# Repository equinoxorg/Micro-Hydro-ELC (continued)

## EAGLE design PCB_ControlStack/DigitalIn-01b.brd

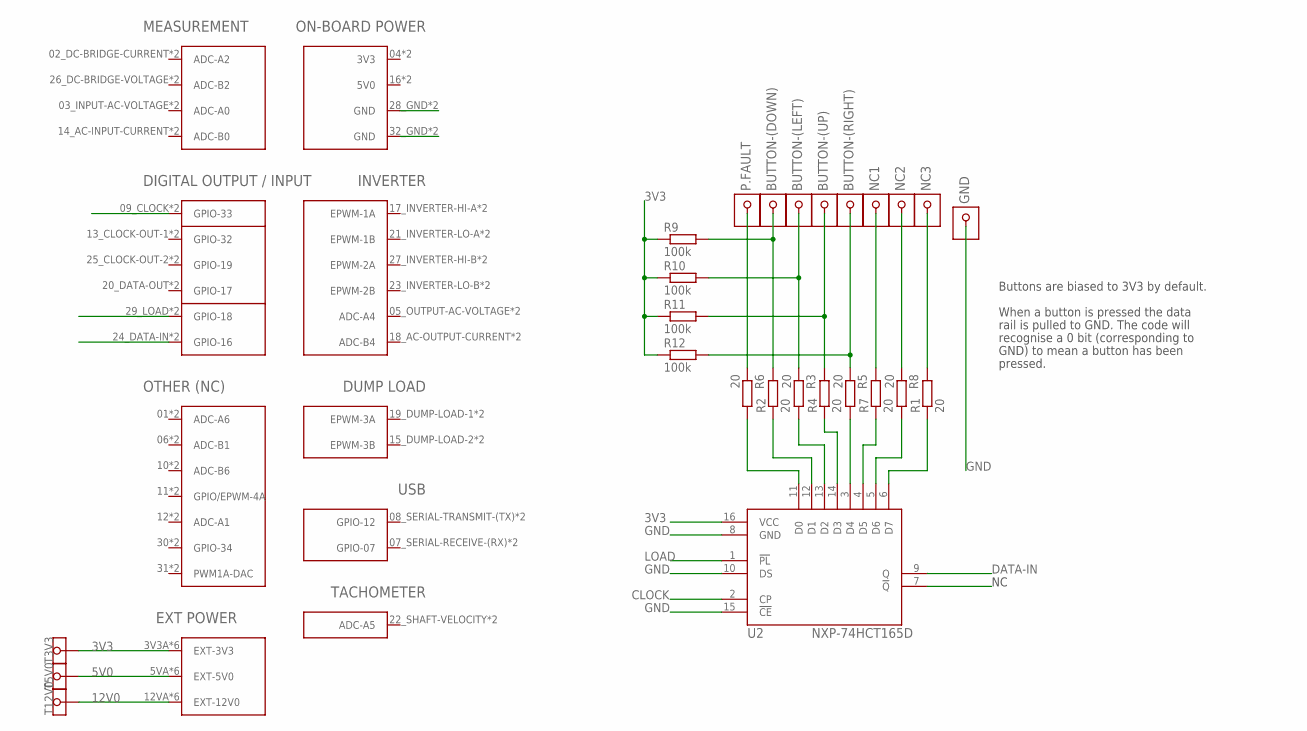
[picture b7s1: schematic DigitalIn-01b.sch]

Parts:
BUTTON-(DOWN): 1X1HEADER(W/VIA)
BUTTON-(LEFT): 1X1HEADER(W/VIA)
BUTTON-(RIGHT): 1X1HEADER(W/VIA)
BUTTON-(UP): 1X1HEADER(W/VIA)
GND: 1X1HEADER(W/VIA)
NC1, NC2, NC3: 1X1HEADER(W/VIA)
P.FAULT: 1X1HEADER(W/VIA)
R1, R2, R3, R4, R5, R6, R7, R8: 20; R0805
R9, R10, R11, R12: 100k; R0805
T3V3, T5V0, T12V0: TESTPAD
U1: CONTROLLER_STACK
U2: NXP-74HCT165D; SOIC-16D

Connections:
3V3: R9.1, R10.1, R11.1, R12.1, T3V3.TP, U1.3V3A (EXT-3V3), U1.3V3B (EXT-3V3), U1.3V3C (EXT-3V3), U1.3V3D (EXT-3V3), U1.3V3E (EXT-3V3), U1.3V3F (EXT-3V3), U2.16 (VCC)
5V0: T5V0.TP, U1.5VA (EXT-5V0), U1.5VB (EXT-5V0), U1.5VC (EXT-5V0), U1.5VD (EXT-5V0), U1.5VE (EXT-5V0), U1.5VF (EXT-5V0)
12V0: T12V0.TP, U1.12VA (EXT-12V0), U1.12VB (EXT-12V0), U1.12VC (EXT-12V0), U1.12VD (EXT-12V0), U1.12VE (EXT-12V0), U1.12VF (EXT-12V0)
CLOCK: U1.09_CLOCK (GPIO-33), U1.C9 (GPIO-33), U2.2 (CP)
DATA-IN: U1.24_DATA-IN (GPIO-16), U1.C24 (GPIO-16), U2.9 (Q)
GND: GND.P$2, GND.P$3, GND.P$4, GND.PAD, U1.28_GND (GND), U1.32_GND (GND), U1.C28 (GND), U1.C32 (GND), U2.8 (GND), U2.10 (DS), U2.15 (!CE)
LOAD: U1.29_LOAD (GPIO-18), U1.C29 (GPIO-18), U2.1 (!PL)
unnamed: R6.2, U2.11 (D0)
unnamed: R2.1, U2.12 (D1)
unnamed: R3.2, U2.13 (D2)
unnamed: R4.1, U2.14 (D3)
unnamed: P.FAULT.P$2, P.FAULT.P$3, P.FAULT.P$4, P.FAULT.PAD, R6.1
unnamed: R7.1, U2.4 (D5)
unnamed: R8.2, U2.5 (D6)
unnamed: R1.1, U2.6 (D7)
unnamed: R5.2, U2.3 (D4)
unnamed: BUTTON-(DOWN).P$2, BUTTON-(DOWN).P$3, BUTTON-(DOWN).P$4, BUTTON-(DOWN).PAD, R2.2, R9.2
unnamed: BUTTON-(LEFT).P$2, BUTTON-(LEFT).P$3, BUTTON-(LEFT).P$4, BUTTON-(LEFT).PAD, R3.1, R10.2
unnamed: BUTTON-(UP).P$2, BUTTON-(UP).P$3, BUTTON-(UP).P$4, BUTTON-(UP).PAD, R4.2, R11.2
unnamed: BUTTON-(RIGHT).P$2, BUTTON-(RIGHT).P$3, BUTTON-(RIGHT).P$4, BUTTON-(RIGHT).PAD, R5.1, R12.2
unnamed: NC1.P$2, NC1.P$3, NC1.P$4, NC1.PAD, R7.2
unnamed: NC2.P$2, NC2.P$3, NC2.P$4, NC2.PAD, R8.1
unnamed: NC3.P$2, NC3.P$3, NC3.P$4, NC3.PAD, R1.2

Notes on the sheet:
Buttons are biased to 3V3 by default.
When a button is pressed the data
rail is pulled to GND. The code will
recognise a 0 bit (corresponding to
GND) to mean a button has been
pressed.

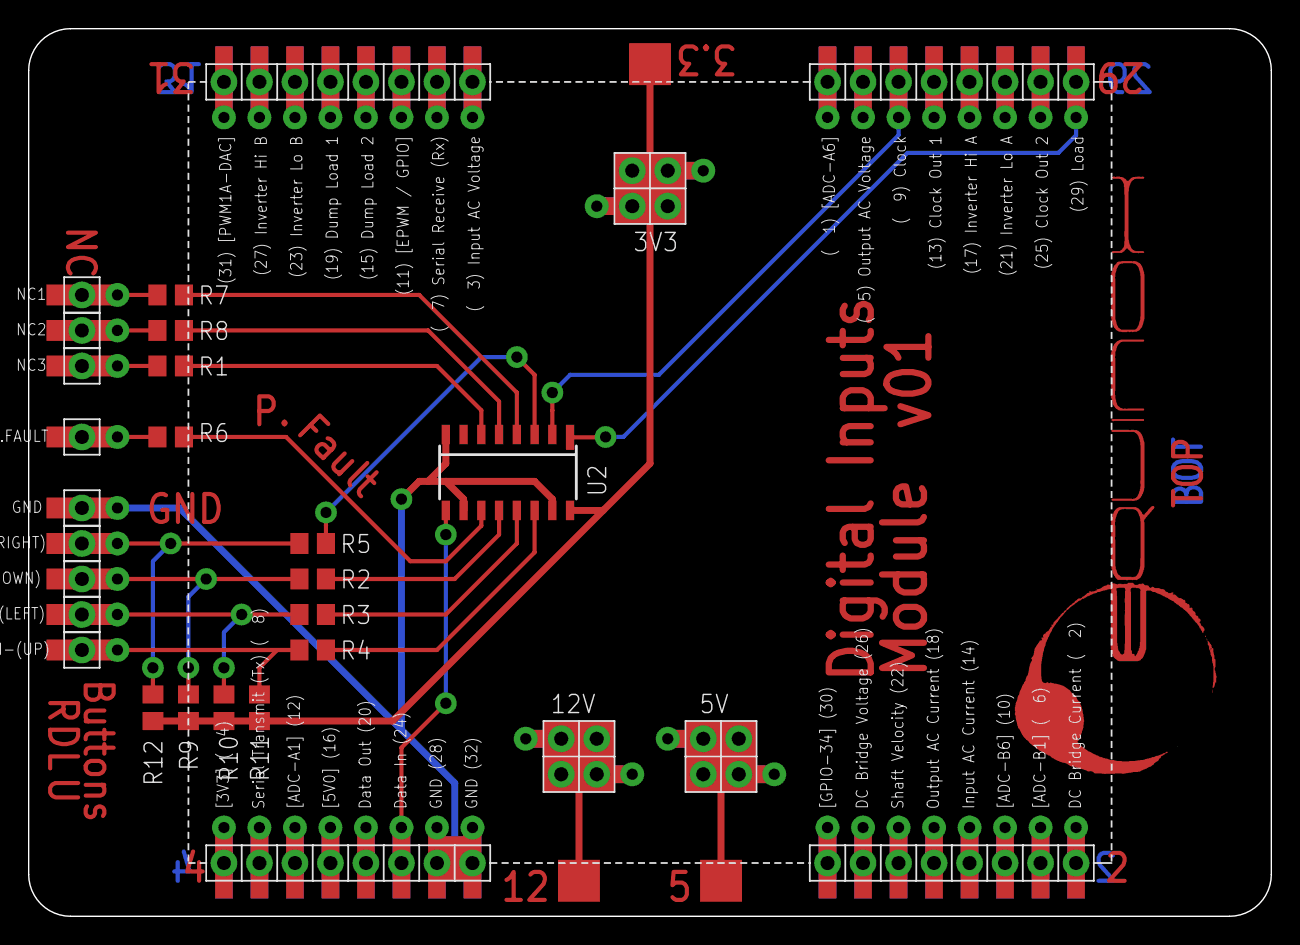
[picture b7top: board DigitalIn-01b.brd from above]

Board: 2 copper layers, 88.9 x 63.5 mm, 26 parts (0 on the bottom side), 23 nets.

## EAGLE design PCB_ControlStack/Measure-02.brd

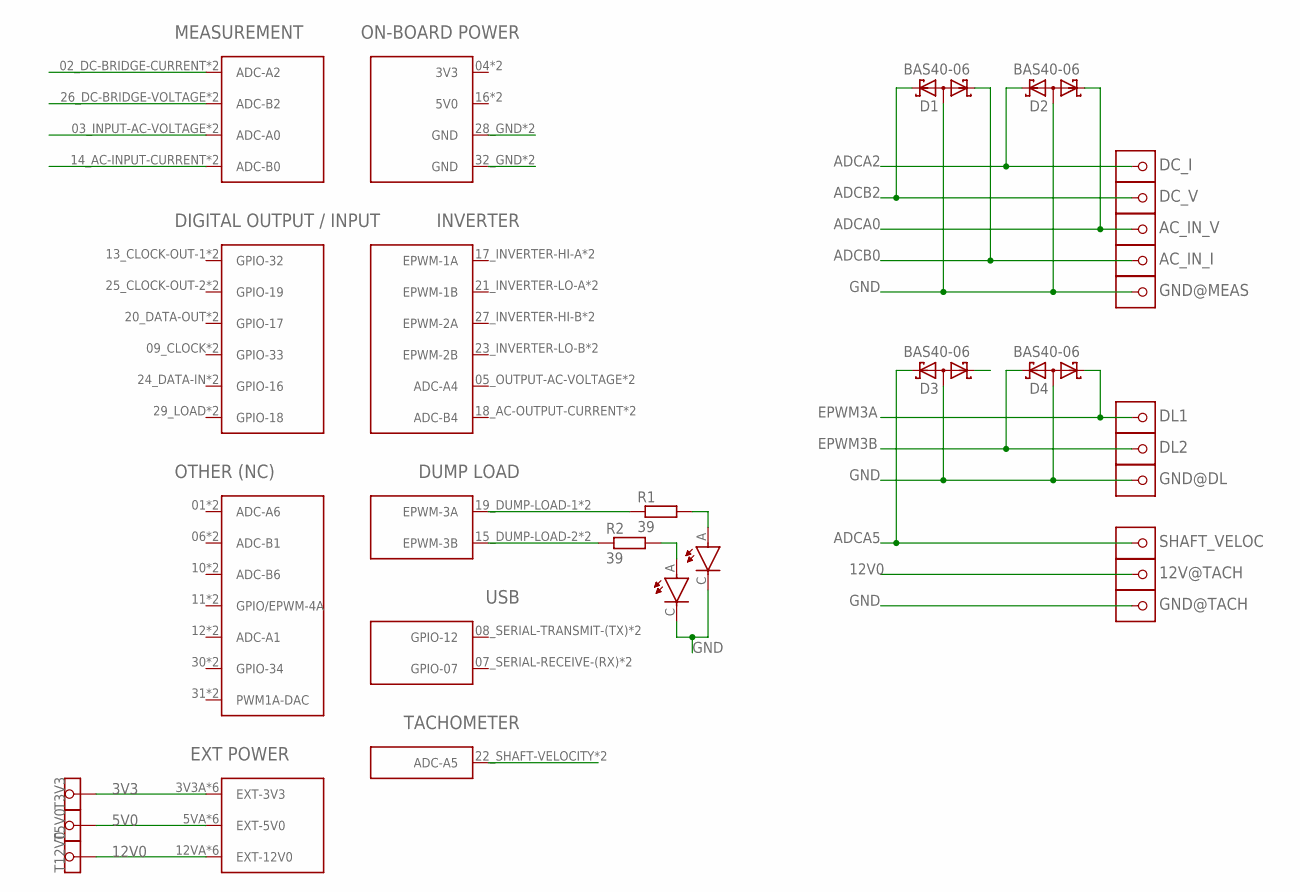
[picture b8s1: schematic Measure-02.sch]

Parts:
12V@TACH: 1X1HEADER(W/VIA)
AC_IN_I: 1X1HEADER(W/VIA)
AC_IN_V: 1X1HEADER(W/VIA)
D1, D2, D3, D4: BAS40-06; SOT23
DC_I: 1X1HEADER(W/VIA)
DC_V: 1X1HEADER(W/VIA)
DL1, DL2: 1X1HEADER(W/VIA)
DL.1, DL.2: PLCC2
GND@DL: 1X1HEADER(W/VIA)
GND@MEAS: 1X1HEADER(W/VIA)
GND@TACH: 1X1HEADER(W/VIA)
R1, R2: 39; R0805
SHAFT_VELOC: 1X1HEADER(W/VIA)
T3V3, T5V0, T12V0: TESTPAD
U$1: CONTROLLER_STACK

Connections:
3V3: T3V3.TP, U$1.3V3A (EXT-3V3), U$1.3V3B (EXT-3V3), U$1.3V3C (EXT-3V3), U$1.3V3D (EXT-3V3), U$1.3V3E (EXT-3V3), U$1.3V3F (EXT-3V3)
5V0: T5V0.TP, U$1.5VA (EXT-5V0), U$1.5VB (EXT-5V0), U$1.5VC (EXT-5V0), U$1.5VD (EXT-5V0), U$1.5VE (EXT-5V0), U$1.5VF (EXT-5V0)
12V0: 12V@TACH.P$2, 12V@TACH.P$3, 12V@TACH.P$4, 12V@TACH.PAD, T12V0.TP, U$1.12VA (EXT-12V0), U$1.12VB (EXT-12V0), U$1.12VC (EXT-12V0), U$1.12VD (EXT-12V0), U$1.12VE (EXT-12V0), U$1.12VF (EXT-12V0)
ADCA0: AC_IN_V.P$2, AC_IN_V.P$3, AC_IN_V.P$4, AC_IN_V.PAD, D2.1 (K1), U$1.03_INPUT-AC-VOLTAGE (ADC-A0), U$1.C3 (ADC-A0)
ADCA2: D2.2 (K2), DC_I.P$2, DC_I.P$3, DC_I.P$4, DC_I.PAD, U$1.02_DC-BRIDGE-CURRENT (ADC-A2), U$1.C2 (ADC-A2)
ADCA5: D3.2 (K2), SHAFT_VELOC.P$2, SHAFT_VELOC.P$3, SHAFT_VELOC.P$4, SHAFT_VELOC.PAD, U$1.22_SHAFT-VELOCITY (ADC-A5), U$1.C22 (ADC-A5)
ADCB0: AC_IN_I.P$2, AC_IN_I.P$3, AC_IN_I.P$4, AC_IN_I.PAD, D1.1 (K1), U$1.14_AC-INPUT-CURRENT (ADC-B0), U$1.C14 (ADC-B0)
ADCB2: D1.2 (K2), DC_V.P$2, DC_V.P$3, DC_V.P$4, DC_V.PAD, U$1.26_DC-BRIDGE-VOLTAGE (ADC-B2), U$1.C26 (ADC-B2)
EPWM3A: D4.1 (K1), DL1.P$2, DL1.P$3, DL1.P$4, DL1.PAD, R1.1, U$1.19_DUMP-LOAD-1 (EPWM-3A), U$1.C19 (EPWM-3A)
EPWM3B: D4.2 (K2), DL2.P$2, DL2.P$3, DL2.P$4, DL2.PAD, R2.1, U$1.15_DUMP-LOAD-2 (EPWM-3B), U$1.C15 (EPWM-3B)
GND: D1.3 (AA), D2.3 (AA), D3.3 (AA), D4.3 (AA), DL.1.C, DL.2.C, GND@DL.P$2, GND@DL.P$3, GND@DL.P$4, GND@DL.PAD, GND@MEAS.P$2, GND@MEAS.P$3, GND@MEAS.P$4, GND@MEAS.PAD, GND@TACH.P$2, GND@TACH.P$3, GND@TACH.P$4, GND@TACH.PAD, U$1.28_GND (GND), U$1.32_GND (GND), U$1.C28 (GND), U$1.C32 (GND)
unnamed: DL.2.A, R2.2
unnamed: DL.1.A, R1.2
STARTUP: D3.1 (K1)

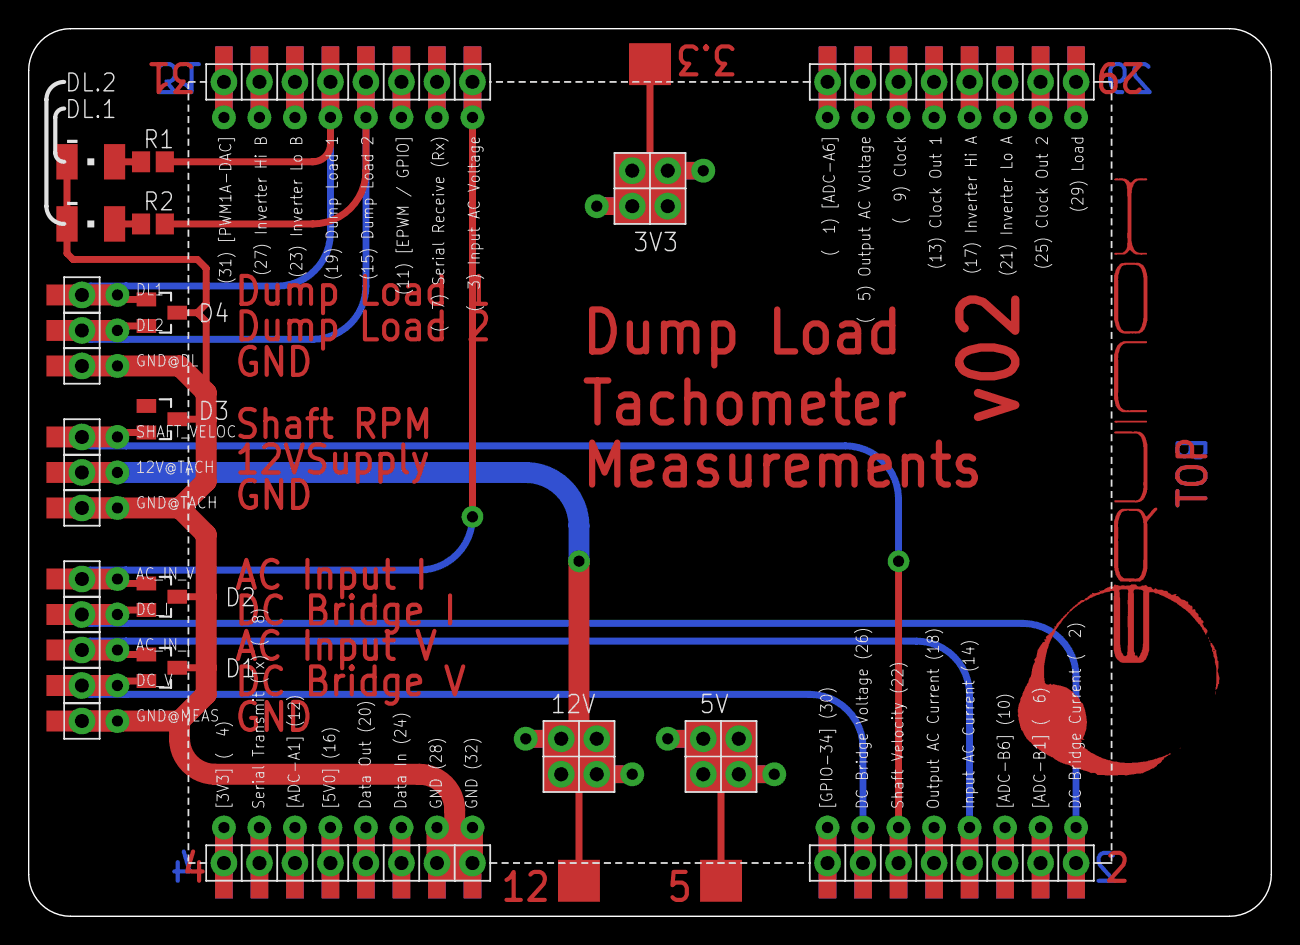
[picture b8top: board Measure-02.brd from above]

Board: 2 copper layers, 88.9 x 63.5 mm, 23 parts (0 on the bottom side), 13 nets.

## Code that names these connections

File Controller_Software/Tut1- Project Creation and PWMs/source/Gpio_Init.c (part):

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	GpioCtrlRegs.GPADIR.all   = 0x00000000;		// All group A GPIO are inputs
	GpioCtrlRegs.GPAPUD.all   = 0x00000FFF;		// Pull-ups enabled GPIO31-12, disabled GPIO11-0

	GpioCtrlRegs.GPAMUX1.bit.GPIO0  = 0;		// 0=GPIO               1=EPWM1A     2=rsvd       3=rsvd
	GpioCtrlRegs.GPAMUX1.bit.GPIO1  = 0;		// 0=GPIO               1=EPWM1B     2=rsvd       3=COMP1OUT
	GpioCtrlRegs.GPAMUX1.bit.GPIO2  = 0;		// 0=GPIO               1=EPWM2A     2=rsvd       3=rsvd
	GpioCtrlRegs.GPAMUX1.bit.GPIO3  = 0;		// 0=GPIO               1=EPWM2B     2=SPISOMIA   3=COMP2OUT
	GpioCtrlRegs.GPAMUX1.bit.GPIO4  = 0;		// 0=GPIO               1=EPWM3A     2=rsvd       3=rsvd
	GpioCtrlRegs.GPAMUX1.bit.GPIO5  = 0;		// 0=GPIO               1=EPWM3B     2=SPISIMOA   3=ECAP1
	GpioCtrlRegs.GPAMUX1.bit.GPIO6  = 0;		// 0=GPIO               1=EPWM4A     2=EPWMSYNCI  3=EPWMSYNCO
	GpioCtrlRegs.GPAMUX1.bit.GPIO7  = 0;		// 0=GPIO               1=EPWM4B     2=SCIRXDA    3=ECAP2
	GpioCtrlRegs.GPAMUX1.bit.GPIO8  = 0;		// 0=GPIO               1=EPWM5A     2=rsvd       3=ADCSOCAO
	GpioCtrlRegs.GPAMUX1.bit.GPIO9  = 0;		// 0=GPIO               1=EPWM5B     2=SCITXDB    3=ECAP3
	GpioCtrlRegs.GPAMUX1.bit.GPIO10 = 0;		// 0=GPIO               1=EPWM6A     2=rsvd       3=ADCSOCBO
	GpioCtrlRegs.GPAMUX1.bit.GPIO11 = 0;		// 0=GPIO               1=EPWM6B     2=SCIRXDB    3=ECAP1
	GpioCtrlRegs.GPAMUX1.bit.GPIO12 = 0;		// 0=GPIO               1=TZ1        2=SCITXDA    3=SPISIMOB
	GpioCtrlRegs.GPAMUX1.bit.GPIO13 = 0;		// 0=GPIO               1=TZ2        2=rsvd       3=SPISOMIB
	GpioCtrlRegs.GPAMUX1.bit.GPIO14 = 0;		// 0=GPIO               1=TZ3        2=SCITXDB    3=SPICLKB
	GpioCtrlRegs.GPAMUX1.bit.GPIO15 = 0;		// 0=GPIO               1=ECAP2      2=SCIRXDB    3=SPISTEB

	GpioCtrlRegs.GPAMUX2.bit.GPIO16 = 0;		// 0=GPIO               1=SPISIMOA   2=rsvd       3=TZ2
	GpioCtrlRegs.GPAMUX2.bit.GPIO17 = 0;		// 0=GPIO               1=SPISOMIA   2=rsvd       3=TZ3
	GpioCtrlRegs.GPAMUX2.bit.GPIO18 = 0;		// 0=GPIO               1=SPICLKA    2=SCITXDB    3=XCLKOUT
	GpioCtrlRegs.GPAMUX2.bit.GPIO19 = 0;		// 0=GPIO/XCLKIN        1=SPISTEA    2=SCIRXDB    3=ECAP1
	GpioCtrlRegs.GPAMUX2.bit.GPIO20 = 0;		// 0=GPIO               1=EQEP1A     2=MDXA       3=COMP1OUT
	GpioCtrlRegs.GPAMUX2.bit.GPIO21 = 0;		// 0=GPIO               1=EQEP1B     2=MDRA       3=COMP2OUT
	GpioCtrlRegs.GPAMUX2.bit.GPIO22 = 0;		// 0=GPIO               1=EQEP1S     2=MCLKXA     3=SCITXDB
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	GpioCtrlRegs.GPBDIR.all   = 0x00000000;		// All group B GPIO are inputs
	GpioCtrlRegs.GPBPUD.all   = 0x00000000;		// All group B pull-ups enabled

	GpioCtrlRegs.GPBMUX1.bit.GPIO32 = 0;		// 0=GPIO               1=SDAA      2=EPWMSYNCI  3=ADCSOCAO
	GpioCtrlRegs.GPBMUX1.bit.GPIO33 = 0;		// 0=GPIO               1=SCLA      2=EPWMSYNCO  3=ADCSOCBO
	GpioCtrlRegs.GPBMUX1.bit.GPIO34 = 0;		// 0=GPIO               1=COMP2OUT  2=rsvd       3=COMP3OUT
	GpioCtrlRegs.GPBMUX1.bit.GPIO35 = 0;		// 0=GPIO (TDI)         1=rsvd      2=rsvd       3=rsvd
	GpioCtrlRegs.GPBMUX1.bit.GPIO36 = 0;		// 0=GPIO (TMS)         1=rsvd      2=rsvd       3=rsvd
	GpioCtrlRegs.GPBMUX1.bit.GPIO37 = 0;		// 0=GPIO (TDO)         1=rsvd      2=rsvd       3=rsvd
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//--- Input or Output Selected Pins
	//	0 = Input (default)
	//	1 = Output
	GpioCtrlRegs.GPADIR.bit.GPIO17 = 0;
	GpioCtrlRegs.GPADIR.bit.GPIO18 = 0;
	GpioCtrlRegs.GPADIR.bit.GPIO19 = 0;
	GpioCtrlRegs.GPBDIR.bit.GPIO32 = 0;
	GpioCtrlRegs.GPBDIR.bit.GPIO33 = 0;
	GpioCtrlRegs.GPBDIR.bit.GPIO34 = 0;			// GPIO34 is an output (connected to LED on F28069 ControlSTICK)

//--- Finish up
	asm(" EDIS");								// Disable EALLOW protected register access
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
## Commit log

2012-08-16 inital commit
2012-08-16 added .gitignore
2012-08-16 protection_board added
2012-08-16 dumpload circuit added
2012-08-16 measurement_board added, still needs check and possible editing for manufacture
2012-08-16 changed directory names
2012-08-17 measurement and exitation added, all boards labeled for manufacturing
2012-08-17 library added, boards labeled with manufacturing id
2012-10-24 Control software files added, c-files headers etc
2012-11-14 Added licence information
2012-11-14 Added software licence
2013-05-15 Control software files added, c-files, headers etc
2013-05-15 Workspace/Project can now be opened in github
2013-05-15 Comment changes made to ADC_Init.c for clarity
2013-05-16 Hydro ELC Control Stack PCBs and Supporting Files
2013-05-25 F28069 Tutorial and Example Files
